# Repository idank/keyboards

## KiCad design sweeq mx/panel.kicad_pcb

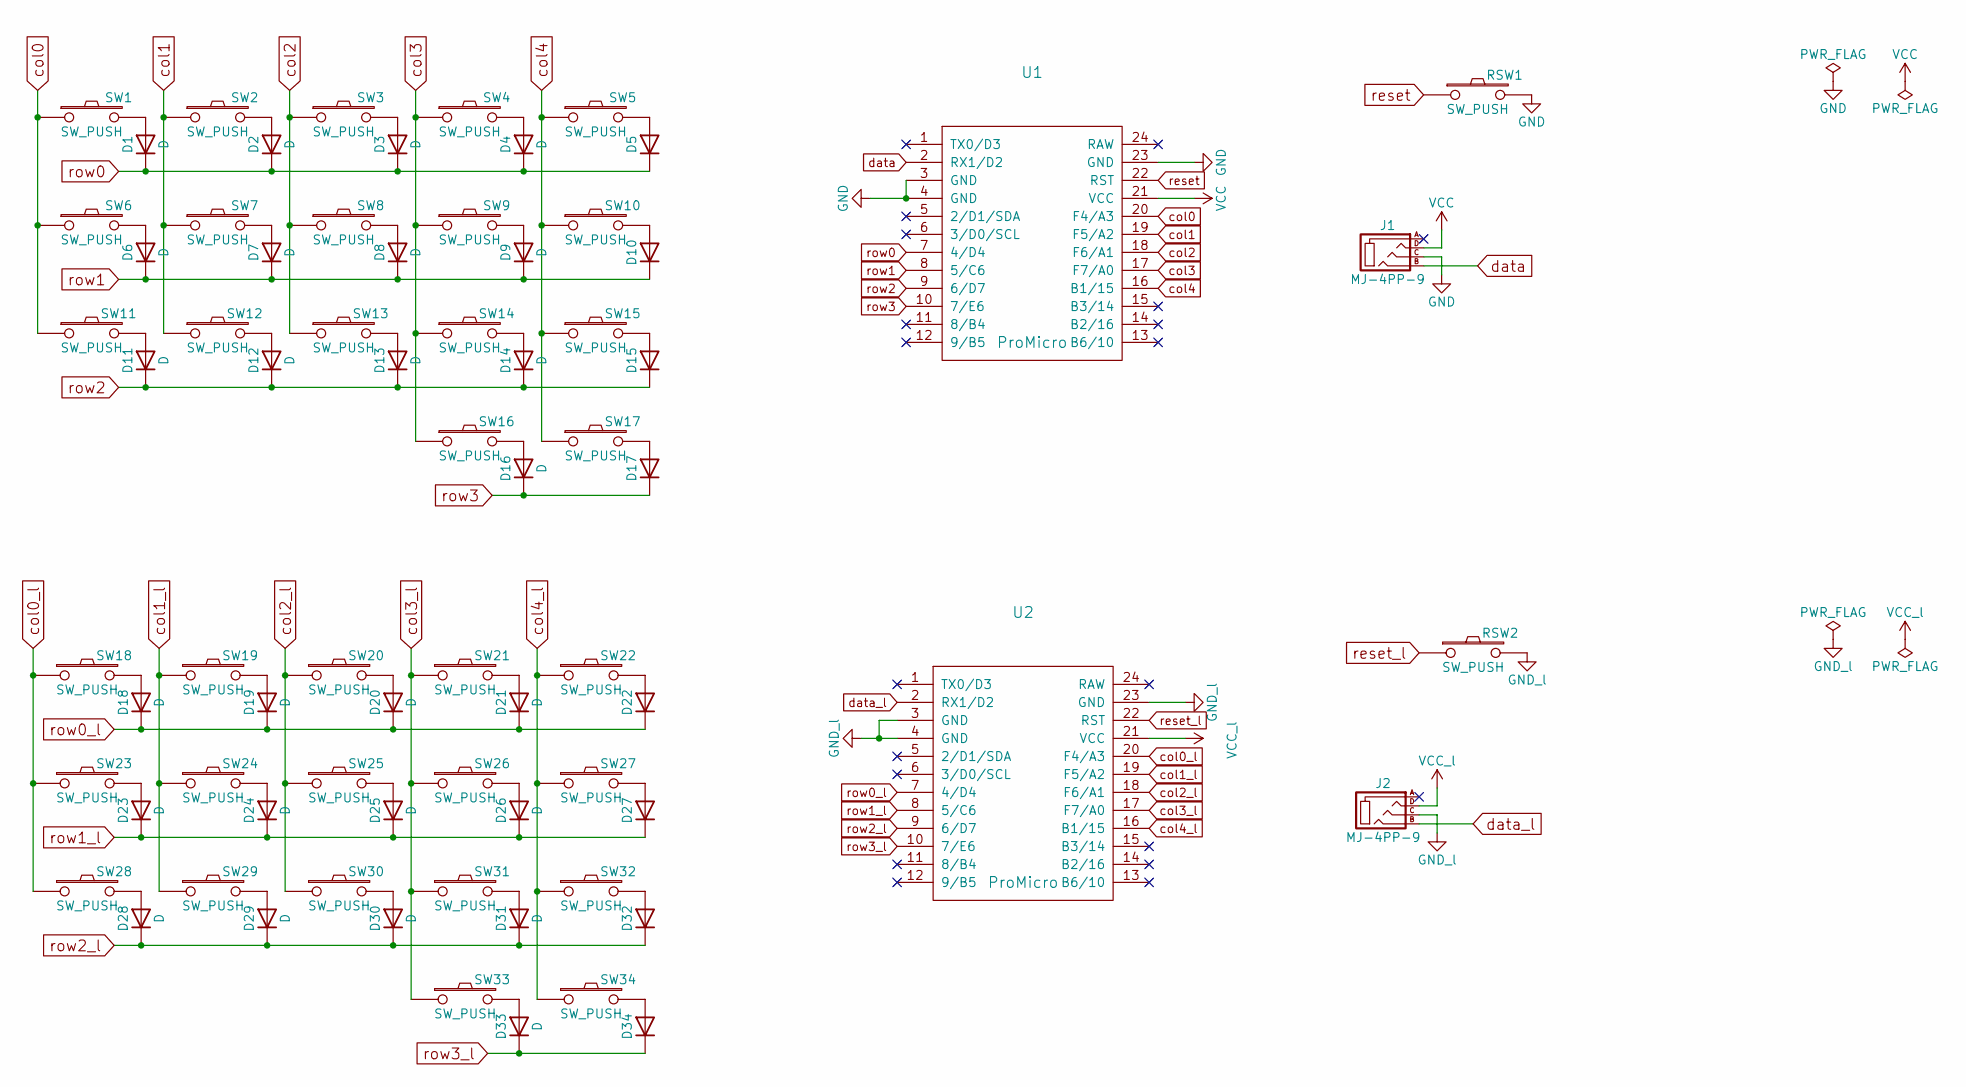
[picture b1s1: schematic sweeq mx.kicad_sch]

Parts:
D1, D2, D3, D4, D5, D6, D7, D8, D9, D10, D11, D12, D13, D14, D15, D16, D17, D18, D19, D20, D21, D22, D23, D24, D25, D26, D27, D28, D29, D30, D31, D32, D33, D34: D; D3_SMD_v2
J1, J2: MJ-4PP-9; MJ-4PP-9_1side
RSW1, RSW2: SW_PUSH; RSW_2PIN_SMD
SW1, SW2, SW3, SW4, SW5, SW6, SW7, SW8, SW9, SW10, SW11, SW12, SW13, SW14, SW15, SW16, SW17, SW18, SW19, SW20, SW21, SW22, SW23, SW24, SW25, SW26, SW27, SW28, SW29, SW30, SW31, SW32, SW33, SW34: SW_PUSH; SW_MX_HS_CPG151101S11_1u
U1, U2: ProMicro; ProMicro_1mm_holes

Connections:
Board_0-GND: J1.C, RSW1.2, U1.3 (GND), U1.4 (GND), U1.23 (GND)
Board_0-GND_l: J2.C, RSW2.2, U2.3 (GND), U2.4 (GND), U2.23 (GND)
Board_0-Net-(D1-A): D1.2 (A), SW1.2
Board_0-Net-(D2-A): D2.2 (A), SW2.2
Board_0-Net-(D3-A): D3.2 (A), SW3.2
Board_0-Net-(D4-A): D4.2 (A), SW4.2
Board_0-Net-(D5-A): D5.2 (A), SW5.2
Board_0-Net-(D6-A): D6.2 (A), SW6.2
Board_0-Net-(D7-A): D7.2 (A), SW7.2
Board_0-Net-(D8-A): D8.2 (A), SW8.2
Board_0-Net-(D9-A): D9.2 (A), SW9.2
Board_0-Net-(D10-A): D10.2 (A), SW10.2
Board_0-Net-(D11-A): D11.2 (A), SW11.2
Board_0-Net-(D12-A): D12.2 (A), SW12.2
Board_0-Net-(D13-A): D13.2 (A), SW13.2
Board_0-Net-(D14-A): D14.2 (A), SW14.2
Board_0-Net-(D15-A): D15.2 (A), SW15.2
Board_0-Net-(D16-A): D16.2 (A), SW16.2
Board_0-Net-(D17-A): D17.2 (A), SW17.2
Board_0-Net-(D18-A): D18.2 (A), SW18.2
Board_0-Net-(D19-A): D19.2 (A), SW19.2
Board_0-Net-(D20-A): D20.2 (A), SW20.2
Board_0-Net-(D21-A): D21.2 (A), SW21.2
Board_0-Net-(D22-A): D22.2 (A), SW22.2
Board_0-Net-(D23-A): D23.2 (A), SW23.2
Board_0-Net-(D24-A): D24.2 (A), SW24.2
Board_0-Net-(D25-A): D25.2 (A), SW25.2
Board_0-Net-(D26-A): D26.2 (A), SW26.2
Board_0-Net-(D27-A): D27.2 (A), SW27.2
Board_0-Net-(D28-A): D28.2 (A), SW28.2
Board_0-Net-(D29-A): D29.2 (A), SW29.2
Board_0-Net-(D30-A): D30.2 (A), SW30.2
Board_0-Net-(D31-A): D31.2 (A), SW31.2
Board_0-Net-(D32-A): D32.2 (A), SW32.2
Board_0-Net-(D33-A): D33.2 (A), SW33.2
Board_0-Net-(D34-A): D34.2 (A), SW34.2
Board_0-VCC: J1.D, U1.21 (VCC)
Board_0-VCC_l: J2.D, U2.21 (VCC)
Board_0-col0: SW1.1, SW6.1, SW11.1, U1.20 (F4/A3)
Board_0-col0_l: SW18.1, SW23.1, SW28.1, U2.20 (F4/A3)
Board_0-col1: SW2.1, SW7.1, SW12.1, U1.19 (F5/A2)
Board_0-col1_l: SW19.1, SW24.1, SW29.1, U2.19 (F5/A2)
Board_0-col2: SW3.1, SW8.1, SW13.1, U1.18 (F6/A1)
Board_0-col2_l: SW20.1, SW25.1, SW30.1, U2.18 (F6/A1)
Board_0-col3: SW4.1, SW9.1, SW14.1, SW16.1, U1.17 (F7/A0)
Board_0-col3_l: SW21.1, SW26.1, SW31.1, SW33.1, U2.17 (F7/A0)
Board_0-col4: SW5.1, SW10.1, SW15.1, SW17.1, U1.16 (B1/15)
Board_0-col4_l: SW22.1, SW27.1, SW32.1, SW34.1, U2.16 (B1/15)
Board_0-data: J1.B, U1.2 (RX1/D2)
Board_0-data_l: J2.B, U2.2 (RX1/D2)
Board_0-reset: RSW1.1, U1.22 (RST)
Board_0-reset_l: RSW2.1, U2.22 (RST)
Board_0-row0: D1.1 (K), D2.1 (K), D3.1 (K), D4.1 (K), D5.1 (K), U1.7 (4/D4)
Board_0-row0_l: D18.1 (K), D19.1 (K), D20.1 (K), D21.1 (K), D22.1 (K), U2.7 (4/D4)
Board_0-row1: D6.1 (K), D7.1 (K), D8.1 (K), D9.1 (K), D10.1 (K), U1.8 (5/C6)
Board_0-row1_l: D23.1 (K), D24.1 (K), D25.1 (K), D26.1 (K), D27.1 (K), U2.8 (5/C6)
Board_0-row2: D11.1 (K), D12.1 (K), D13.1 (K), D14.1 (K), D15.1 (K), U1.9 (6/D7)
Board_0-row2_l: D28.1 (K), D29.1 (K), D30.1 (K), D31.1 (K), D32.1 (K), U2.9 (6/D7)
Board_0-row3: D16.1 (K), D17.1 (K), U1.10 (7/E6)
Board_0-row3_l: D33.1 (K), D34.1 (K), U2.10 (7/E6)
Board_0-unconnected-(J1-PadA): J1.A
Board_0-unconnected-(J2-PadA): J2.A
Board_0-unconnected-(U1-2/D1/SDA-Pad5): U1.5 (2/D1/SDA)
Board_0-unconnected-(U1-3/D0/SCL-Pad6): U1.6 (3/D0/SCL)
Board_0-unconnected-(U1-8/B4-Pad11): U1.11 (8/B4)
Board_0-unconnected-(U1-9/B5-Pad12): U1.12 (9/B5)
Board_0-unconnected-(U1-B2/16-Pad14): U1.14 (B2/16)
Board_0-unconnected-(U1-B3/14-Pad15): U1.15 (B3/14)
Board_0-unconnected-(U1-B6/10-Pad13): U1.13 (B6/10)
Board_0-unconnected-(U1-RAW-Pad24): U1.24 (RAW)
Board_0-unconnected-(U1-TX0/D3-Pad1): U1.1 (TX0/D3)
Board_0-unconnected-(U2-2/D1/SDA-Pad5): U2.5 (2/D1/SDA)
Board_0-unconnected-(U2-3/D0/SCL-Pad6): U2.6 (3/D0/SCL)
Board_0-unconnected-(U2-8/B4-Pad11): U2.11 (8/B4)
Board_0-unconnected-(U2-9/B5-Pad12): U2.12 (9/B5)
Board_0-unconnected-(U2-B2/16-Pad14): U2.14 (B2/16)
Board_0-unconnected-(U2-B3/14-Pad15): U2.15 (B3/14)
Board_0-unconnected-(U2-B6/10-Pad13): U2.13 (B6/10)
Board_0-unconnected-(U2-RAW-Pad24): U2.24 (RAW)
Board_0-unconnected-(U2-TX0/D3-Pad1): U2.1 (TX0/D3)

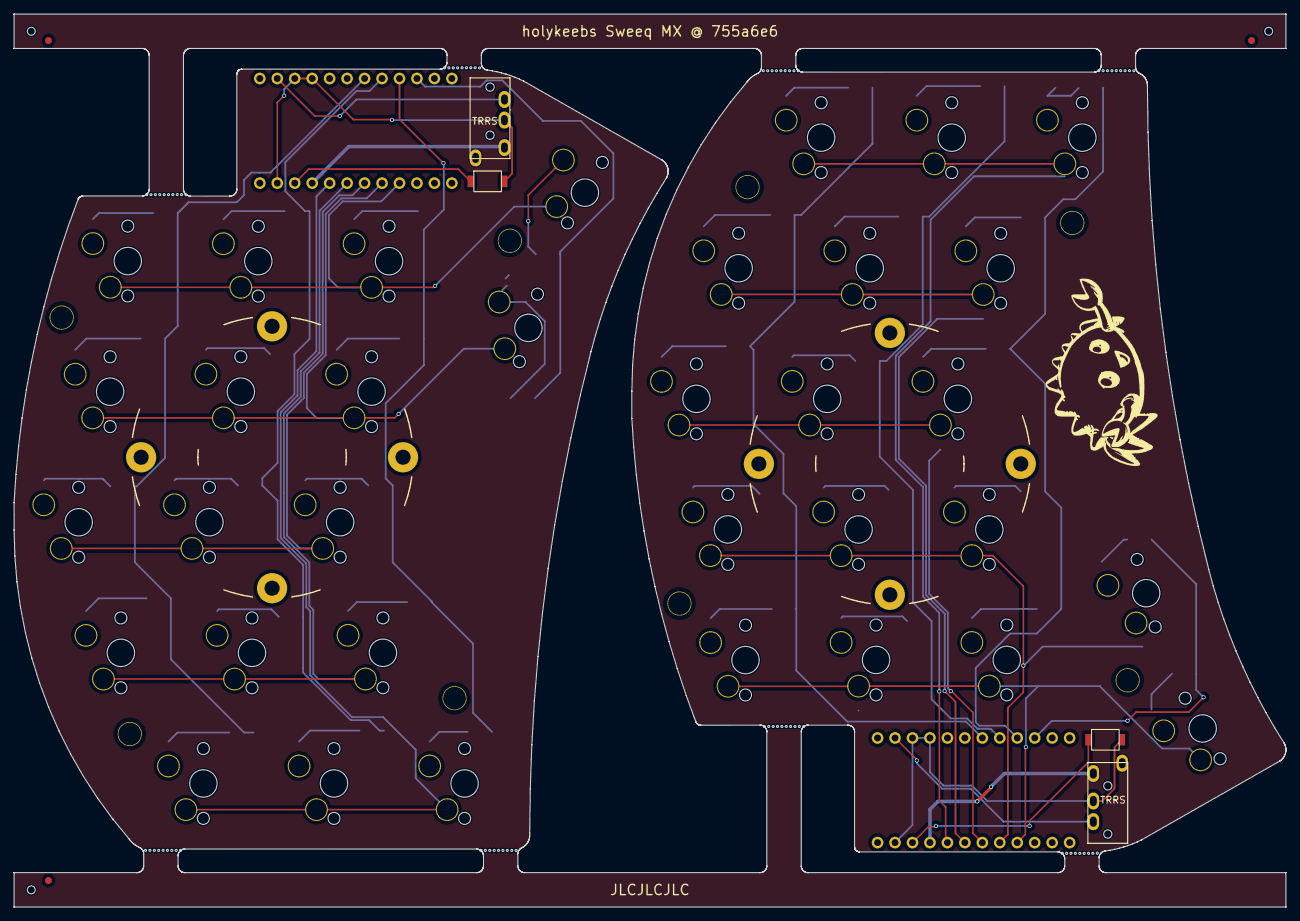
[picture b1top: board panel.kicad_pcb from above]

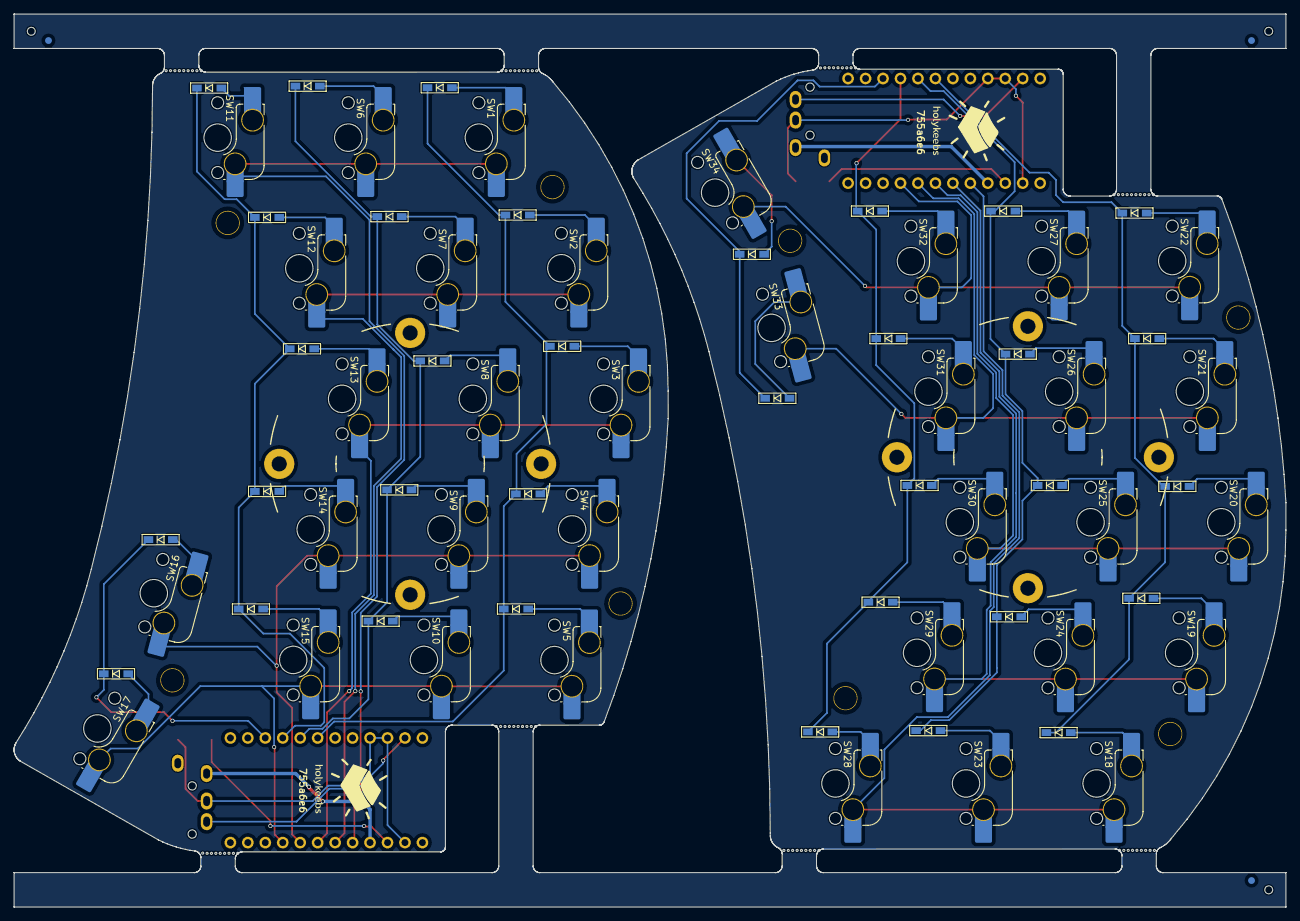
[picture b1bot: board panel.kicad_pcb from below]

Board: 2 copper layers, 185.0 x 129.9 mm, 165 parts (71 on the bottom side), 60 nets.

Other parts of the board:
KiKit_FID_B_1, KiKit_FID_B_2, KiKit_FID_B_3: Fiducial
KiKit_FID_T_1, KiKit_FID_T_2, KiKit_FID_T_3: Fiducial
KiKit_MB_1_2, KiKit_MB_1_3, KiKit_MB_1_4, KiKit_MB_1_5, KiKit_MB_1_6, KiKit_MB_1_7, KiKit_MB_1_8, KiKit_MB_1_9, KiKit_MB_1_10, KiKit_MB_2_2, KiKit_MB_2_3, KiKit_MB_2_4, KiKit_MB_2_5, KiKit_MB_2_6, KiKit_MB_2_7, KiKit_MB_2_8, KiKit_MB_2_9, KiKit_MB_2_10, KiKit_MB_3_2, KiKit_MB_3_3, KiKit_MB_3_4, KiKit_MB_3_5, KiKit_MB_3_6, KiKit_MB_3_7, KiKit_MB_3_8, KiKit_MB_3_9, KiKit_MB_3_10, KiKit_MB_3_11, KiKit_MB_4_3, KiKit_MB_4_4, KiKit_MB_4_5, KiKit_MB_4_6, KiKit_MB_4_7, KiKit_MB_4_8, KiKit_MB_4_9, KiKit_MB_4_10, KiKit_MB_4_11, KiKit_MB_5_3, KiKit_MB_5_4, KiKit_MB_5_5, KiKit_MB_5_6, KiKit_MB_5_7, KiKit_MB_5_8, KiKit_MB_5_9, KiKit_MB_5_10, KiKit_MB_5_11, KiKit_MB_6_3, KiKit_MB_6_4, KiKit_MB_6_5, KiKit_MB_6_6, KiKit_MB_6_7, KiKit_MB_6_8, KiKit_MB_6_9, KiKit_MB_6_10, KiKit_MB_6_11, KiKit_MB_7_2, KiKit_MB_7_3, KiKit_MB_7_4, KiKit_MB_7_5, KiKit_MB_7_6, KiKit_MB_7_7, KiKit_MB_7_8, KiKit_MB_7_9, KiKit_MB_7_10, KiKit_MB_7_11, KiKit_MB_8_2, KiKit_MB_8_3, KiKit_MB_8_4, KiKit_MB_8_5, KiKit_MB_8_6, KiKit_MB_8_7, KiKit_MB_8_8, KiKit_MB_8_9, KiKit_MB_8_10: NPTH
KiKit_TO_1, KiKit_TO_2, KiKit_TO_3: NPTH
Mounting 01, Mounting 01#2, Mounting 02, Mounting 02#2, Mounting 03, Mounting 03#2, Mounting 04, Mounting 04#2: M2_SPACER
